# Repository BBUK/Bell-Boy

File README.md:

# Bell-Boy
NEW VERSION IMMINENT - THIS REPOSITORY CONTAINS A GREAT DEAL OF CODE AND INFORMATION IN FLUX BETWEEN VERSIONS SO SHOULD NOT BE RELIED UPON

This repository contains the code and hardware design for the Bell-Boy Project.  

The Bell-Boy is a device used to measure how hard a person pulls on a tower bell rope.  I hope it will be a useful training aid.  

## Hardware

The core of the hardware comprises a Raspberry Pi Zero and a PCB mounted on it containing an IMU IC (an ICM20689), a ATMEGA328 with the Arduino bootloader and power management and battery charging circuitry.  The Arduino manages battery charging, controls a LED and also stores device calibration data.  The battery is a LiPo integral to the device and is charged via power sourced from the Rasperry Pi's micro USB power socket.  The wiki gives construction information if you want to build your own.

The various files and a description of what they do is set out below

This is the second version of the hardware.  The first version was designed to be mounted on top of the headstock.  More accurate measurements were found to have been achieved by mounting the device closer to the gudgeon pins of the bell.  That required the device to be smaller, which required a LiPo battery. As I could not find a case that would fit a Pi0 and one of the AA sized LiPo batteries, a "flat" LiPo was used which then needed associated charging paraphernalia.

Despite only using one consumer-grade IMU, the second version is *much* more accurate than the first.  There is virtually zero drift in angular readings for all three axes (less than 0.3 degrees per hour).  Acceleration measurements are similarly improved.

## Software

### setupBB.sh

This script takes a stock installation of Arch Linux Arm (for the Raspberry Pi) and adds all scripts and installs all required packages to set up the software environment.  See the wiki for more details 

### grabber

This folder contains the source for two small executables.  

The first, "grabber" takes data from the IMU, transforms it into angle, rotational velocity and rotational acceleration and pushes the data to the users browser via a websocket.  As the force applied by the ringer on the rope needs to be distinguished from gravity, vibration and sensor noise, the solution:

(a) oversamples data from the IMUs (sensors output at 500Hz but the user sees 125Hz).

(b) uses a straightforward Mahony-type filter to calculate angles (I previously used the extended Kalman filter (from https://github.com/hhyyti/dcm-imu) to calculate bell angle but it produced no better results in this application).

(c) uses a Savitsky-Golay filter to smooth the measured rotational acceleration

(d) requires an one-time calibration of the IMU system (from https://bitbucket.org/alberto_pretto/imu_tk).  This is a really useful method of scale and bias calibration that does not require the IMU to be exactly positioned.

The grabber communicates with the user's broswer via websocketd (https://github.com/joewalnes/websocketd). 

The second executable "powermonitor" monitors battery level reports from the Arduino and shuts down the Pi if he battery is too low.  It only operates when the grabber is not running (the grabber only runs when there is an active websocket connection to the user's browser - if there is such a connection, the grabber takes over power monitoring).

### bellboy.js

The Javascript that takes the data from the Bell-Boy and presents it to the users browser.  The browser must support HTML5 and websockets.  More details for operation are in the wiki.

### index.html

Index file.  Note that this file and the JS reference certain image files (icons used to control the front end).  These were licensed in my me but whilst I am permitted to include them on websites that I operate or in code that I distribute, I am not permitted to make them available in a separately downloadable form.

### help.html

Help html file served by the Bell-Boy device.

### utility

Some useful utility programs and files.  There is some information here on installing imu_tk (and in particular ceres-solver which is used by imu_tk).

### arduino

Contains the Arduino program running on the "Arduino'd" ATMEGA328 on the Bell-Boy PCB

### old 

Contains some old code and in particular some code for BNO080 interfacing over the Raspberry Pi's SPI which some people may find useful.  I am no longer using the BNO080 so don't expect this code to be updated.

# Donations!
[Donations](https://paypal.me/PBUK) to this project are welcome :)

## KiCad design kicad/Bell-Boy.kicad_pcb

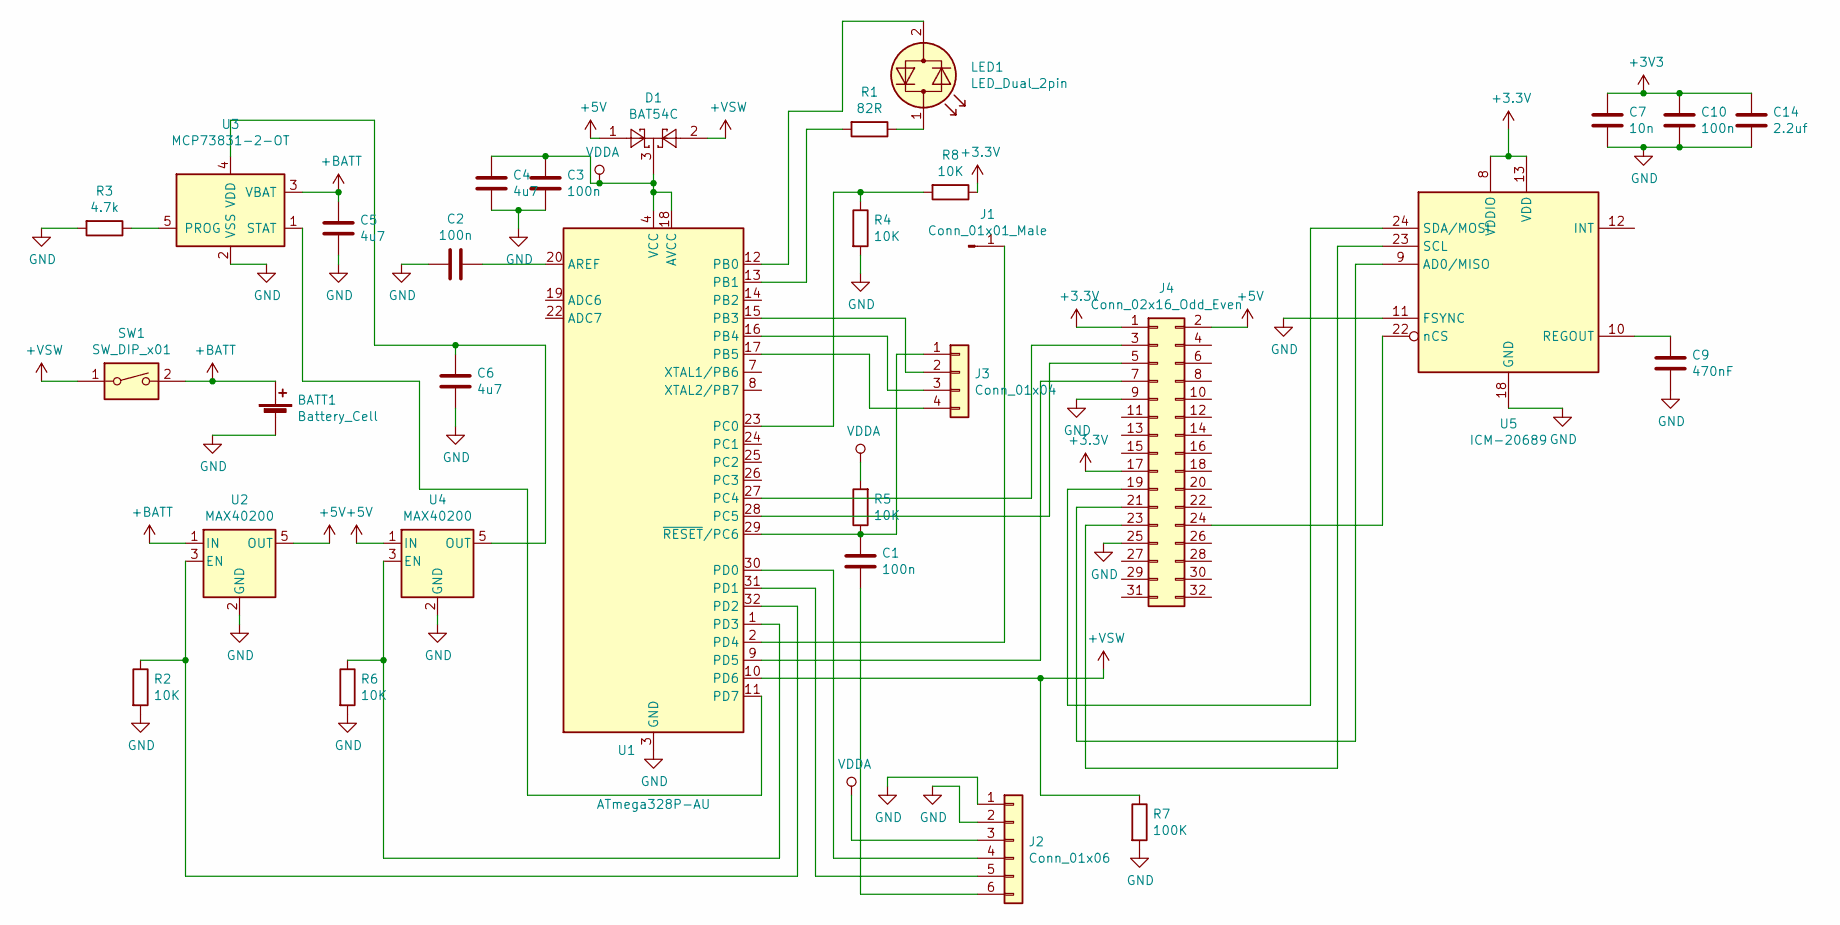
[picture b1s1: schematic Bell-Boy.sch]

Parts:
BATT1: Battery_Cell; PinHeader_1x02_P2.54mm_Vertical
C1, C2, C3, C10: 100n; C_1206_3216Metric_Pad1.42x1.75mm_HandSolder
C4, C5, C6: 4u7; C_1206_3216Metric_Pad1.42x1.75mm_HandSolder
C7: 10n; C_1206_3216Metric_Pad1.42x1.75mm_HandSolder
C9: 470nF; C_1206_3216Metric_Pad1.42x1.75mm_HandSolder
C14: 2.2uf; C_1206_3216Metric_Pad1.42x1.75mm_HandSolder
D1: BAT54C; SOT-23
J1: Conn_01x01_Male; PinHeader_1x01_P2.54mm_Vertical
J2: Conn_01x06; PinHeader_1x06_P2.54mm_Vertical
J3: Conn_01x04; PinHeader_1x04_P2.54mm_Vertical
J4: Conn_02x16_Odd_Even; PinSocket_2x16_P2.54mm_Vertical_SMD
LED1: LED_Dual_2pin; PinHeader_1x02_P2.54mm_Vertical
R1: 82R; R_1206_3216Metric_Pad1.42x1.75mm_HandSolder
R2, R4, R5, R6, R8: 10K; R_1206_3216Metric_Pad1.42x1.75mm_HandSolder
R3: 4.7k; R_1206_3216Metric_Pad1.42x1.75mm_HandSolder
R7: 100K; R_1206_3216Metric_Pad1.42x1.75mm_HandSolder
SW1: SW_DIP_x01; SW_Tactile_SPST_Angled_PTS645Vx39-2LFS
U1: ATmega328P-AU; LQFP-32_7x7mm_P0.8mm
U2, U4: MAX40200; SOT-23-5
U3: MCP73831-2-OT; SOT-23-5
U5: ICM-20689; InvenSense_QFN-24_4x4mm_P0.5mm

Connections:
+5V: D1.1, J4.2, U2.5 (OUT), U4.1 (IN)
+BATT: BATT1.1 (+), C5.1, SW1.2, U2.1 (IN), U3.3 (VBAT)
+VSW: D1.2, R7.1, SW1.1, U1.10 (PD6)
GND: BATT1.2 (-), C2.2, C3.2, C4.2, C5.2, C6.2, C7.2, C9.2, C10.2, C14.2, J2.1, J2.2, J4.9, J4.25, R2.2, R3.2, R4.2, R6.2, R7.2, U1.3 (GND), U1.5 (GND), U1.21 (GND), U2.2 (GND), U3.2 (VSS), U4.2 (GND), U5.11 (FSYNC), U5.18 (GND)
unnamed: C1.1, J3.1, R5.1, U1.29 (~RESET~/PC6)
unnamed: C1.2, J2.6
unnamed: C2.1, U1.20 (AREF)
unnamed: C6.1, U3.4 (VDD), U4.5 (OUT)
unnamed: C9.1, U5.10 (REGOUT)
unnamed: J1.1, U1.2 (PD4)
unnamed: J2.4, U1.30 (PD0)
unnamed: J2.5, U1.31 (PD1)
unnamed: J3.2, U1.15 (PB3)
unnamed: J3.3, U1.16 (PB4)
unnamed: J3.4, U1.17 (PB5)
unnamed: J4.3, U1.27 (PC4)
unnamed: J4.5, U1.28 (PC5)
unnamed: J4.7, U1.9 (PD5)
unnamed: J4.19, U5.24 (SDA/MOSI)
unnamed: J4.21, U5.9 (AD0/MISO)
unnamed: J4.23, U5.23 (SCL)
unnamed: J4.24, U5.22 (nCS)
unnamed: LED1.1 (KA), R1.1
unnamed: LED1.2 (AK), U1.12 (PB0)
unnamed: R1.2, U1.13 (PB1)
unnamed: R2.1, U1.32 (PD2), U2.3 (EN)
unnamed: R3.1, U3.5 (PROG)
unnamed: R4.1, R8.2, U1.23 (PC0)
unnamed: R6.1, U1.1 (PD3), U4.3 (EN)
unnamed: U1.11 (PD7), U3.1 (STAT)
VDDA: C3.1, C4.1, D1.3, J2.3, R5.2, U1.4 (VCC), U1.6 (VCC), U1.18 (AVCC)

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
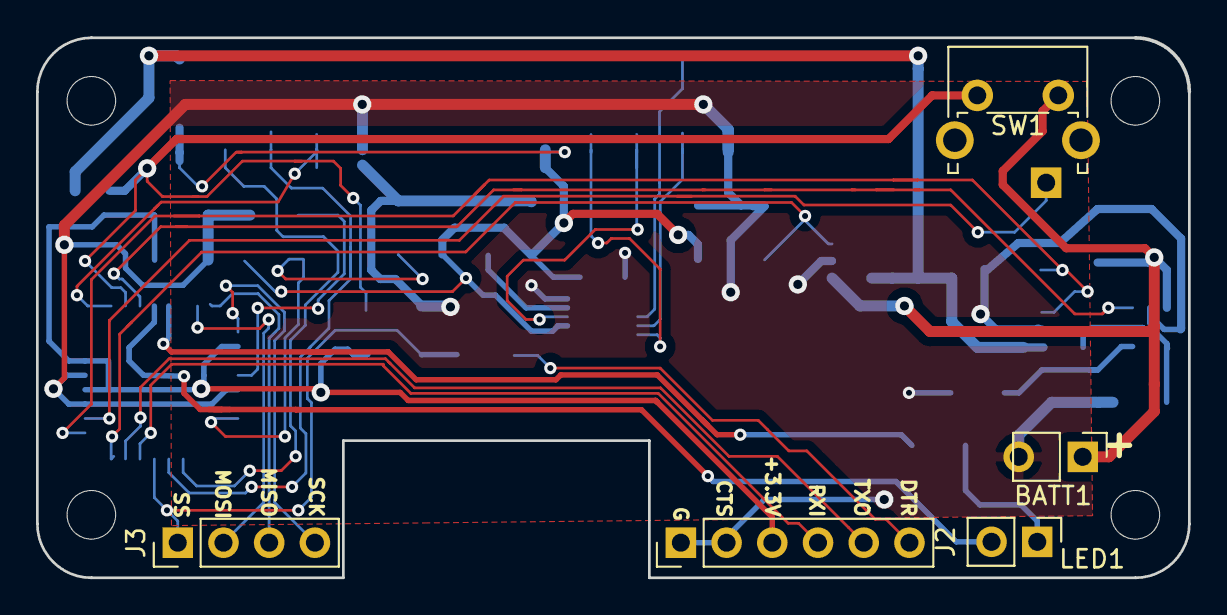
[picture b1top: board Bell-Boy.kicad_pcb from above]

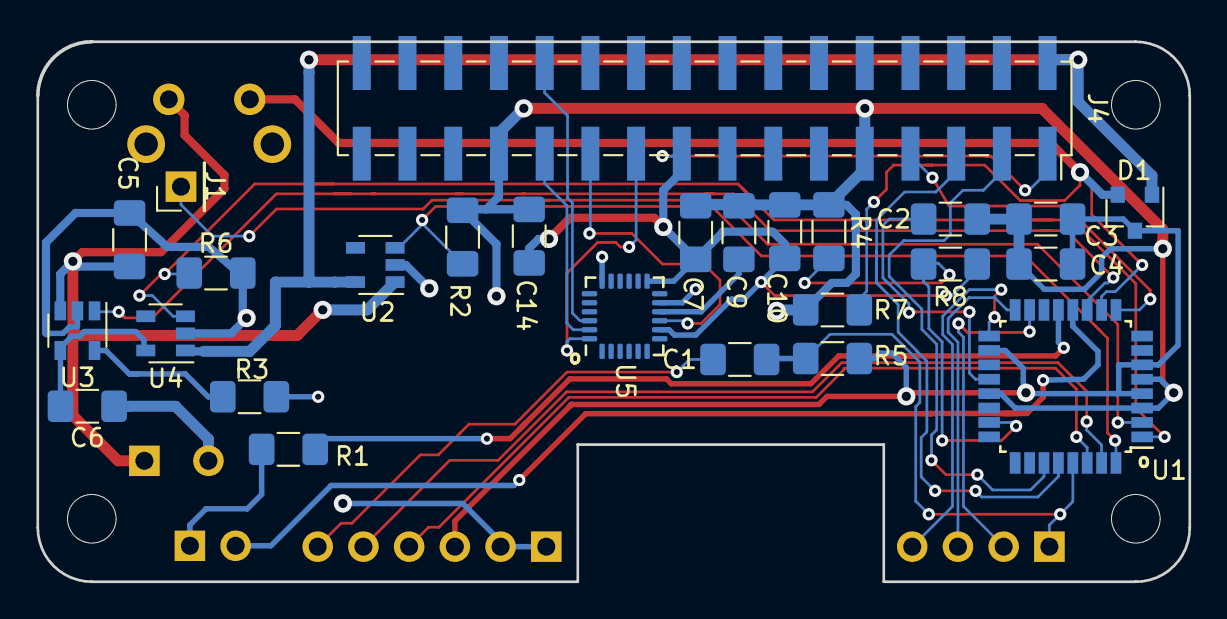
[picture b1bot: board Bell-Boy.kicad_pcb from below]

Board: 2 copper layers, 64.0 x 30.0 mm, 31 parts (26 on the bottom side), 32 nets.

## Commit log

2017-07-07 Formatting, correcting gyro
2017-07-09 Fixed gyro scaling
2017-07-10 Correct sign of a(tang)
2017-07-10 Focus for record textbox
2017-07-10 Code cleanup
2017-07-10 Further code cleanup
2017-07-17 Added utilities
2017-07-17 Corrected utilities
2017-07-17 Update processfile
2017-07-19 Add test scripts
2017-07-19 Correct typo
2017-07-26 Added gyro only test
2017-07-27 Add RTIMULIB version to tests
2017-07-27 Indentation
2018-01-21 Updates...
2018-01-29 Further updates and fixes
2018-01-30 Update bellboy.js with bug fixes
2018-01-31 Implement gyro bias
2018-01-31 Not the last person to be caught by == and =
2018-02-03 Uploaded PCB files
2018-02-06 Add calibration system
2018-02-09 Bugfix - angle_correction not to be preserved across sessions
2018-02-09 Bug fixes
    Swings were not displaying properly and calculate function was not working.
2018-02-09 Update zoomSelect and scaleSelect
2018-02-09 index.html fix
2018-02-09 index.html again
2018-02-10 Finalised(ish) calibration
2018-02-11 New calibration method
2018-02-13 PCB and other updates
2018-02-13 Minor fix
2018-02-14 Images for wiki
2018-02-15 Images, spelling and bugs!
2018-02-15 File permissions
2018-02-16 Tweaks (IE compatibility) and images
2018-02-17 Fix image
2018-02-17 More updates...
2018-02-18 Decided to try nudging again
2018-02-18 More images
2018-02-21 Updates and more images
2018-02-21 Updates and images
2018-02-25 New overlay method (ex timers)...
2018-02-25 New overlay method (ex timers and images)...
2018-02-27 Completed new overlay method
2018-02-27 Tidy-ups
2018-02-27 Updated images
2018-03-04 Internals image
2018-03-06 Added MPU6050 dual IMU code
2018-03-07 Buggettes ...
2018-03-09 Decided to commit to MPU6050
2018-03-16 Automated all calibration. Updated PCB
2018-03-18 Wifi fix, images, simplify local
2018-03-19 Image pack install
2018-03-21 New test, fix images
2018-03-24 image of external wifi
2018-03-25 80211n. Help file and images.
2018-03-27 PCB update and tidy-ups
2018-03-28 Updated licence
2018-03-28 Changes to use gpio config.txt command (commented out presently)
2018-04-07 Tidy ups and prep for session nav
2018-05-22 Updates and corrections
2018-08-27 Side mounting
2018-09-08 Initial stave functionality added
2018-09-09 Finished stave functionality
2018-09-09 Clean images
2018-09-09 Bug fix
2018-09-09 Better centering on stave
2018-10-09 BNO080 trial and minor fix
2018-10-10 BNO080 updates
2018-10-14 Added BNO080 grabber
2018-10-27 Oops
2018-10-28 Bugs
2018-11-11 More updates
2018-11-11 Tidy ups
2018-12-01 GIRV test
2018-12-04 Simplify grabber code
2018-12-04 Update setup
2018-12-04 Update 400Hz
2018-12-08 Rebase to BNO080
2018-12-09 Corrections
2018-12-11 Clarifications
2018-12-11 Preserve old code
2018-12-25 Eye candy prep
2018-12-31 Eye candy done and further updates
2019-01-06 Introduced Savitzky–Golay filter and other changes
2019-01-08 Improve web standards compliancy
2019-01-11 Bugs and updates
2019-01-12 Move back to GIRV
2019-01-15 Updater completed. Added Arduino file
2019-01-30 Initialisation bug fix
2019-02-03 Make initialisation changes more robust and dual MPU6050 code
2019-02-21 Updates to new case format
2019-03-17 Major updates to ICM20689 and fixes
2019-03-17 Calibration setup and fixes
2019-03-17 Update PCB files
2019-03-18 Repushed Kicad files
2019-03-20 Made calibration more robust against overflows
2019-03-30 Updates to calibration
2019-03-31 Calibration improvements. Eye candy now uses quaternion. Commit to Mahony filter.
2019-04-06 Fixed yukky interaction between powermonitor and grabber (and race condition)
2019-04-15 Bug fix for calibrate function.
2019-04-22 Start updates to single IMU
2019-04-28 Finished autotare and single IMU conversion
2019-05-19 Partial completion of ding dong detector and movement of gravity calibration to device. Removed dcm_imu.
2019-06-05 Diagnostics display added. Bell timings now stored and loaded.
2019-06-13 UI updates done. Getting reading to release.
2019-06-13 New image
2019-06-13 Another image
2019-06-14 More images. Timing adjustments in separate modal.
2019-06-18 More accurate chime detection.
2019-06-19 Yet more images!
2019-06-22 Sleep mode and help file
2019-06-22 Sleep mode done
2019-06-23 Small changes
2019-06-30 Tidy ups and consistency
2019-07-01 Update ATmega.
2019-07-03 Correcting all the errors I made when rebasing to 500Hz(!). Slight benefit in having -03 compile optimisation. Updated FirstSample to new format. Added hotplate sketch.
2019-07-04 Tested calibration process on Buster/Pi4
2019-07-05 Changed SavGol filter length after testing at 500Hz. Minor bug fix.
2019-07-13 Some code rejigging. Rope effect calibration for testing.
2019-07-20 Getting ready for release. Improvements to rope adjustments
2019-07-22 Tidy ups and improved chime detection.
2019-07-27 PCB updates, scales now easier to read
2019-07-29 Made calibration more robust against overflows.
2019-08-09 Minor updates
2019-08-18 More small changes
2019-08-20 Corrected a couple of errors in last commit, introduced Kalman filter for testing
2019-08-23 Fixed Kalman instability
2019-08-25 Added simpler calibration option.
2019-08-31 Retired Kalman filter. More quaternion rotation stuff.
